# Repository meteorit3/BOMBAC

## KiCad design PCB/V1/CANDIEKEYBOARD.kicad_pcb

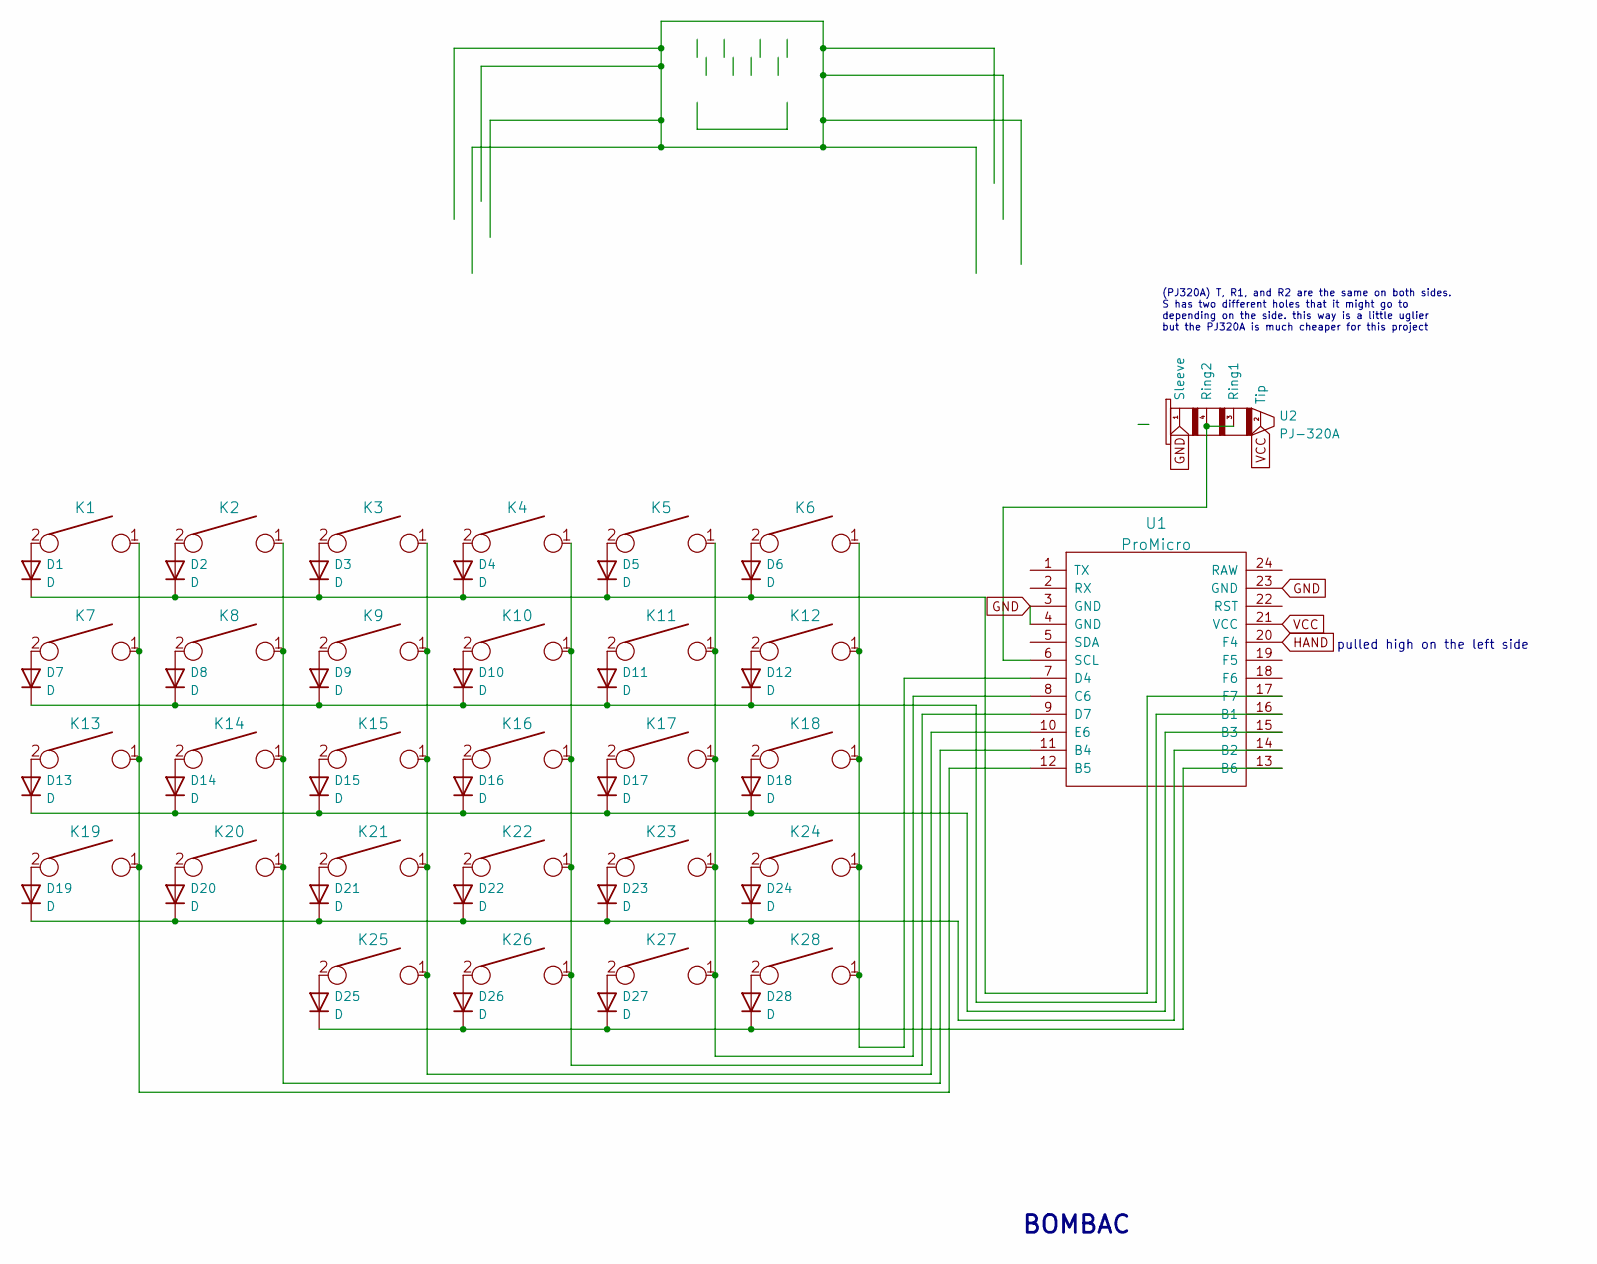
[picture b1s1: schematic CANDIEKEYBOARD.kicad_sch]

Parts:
D1, D2, D3, D4, D5, D6, D7, D8, D9, D10, D11, D12, D13, D14, D15, D16, D17, D18, D19, D20, D21, D22, D23, D24, D25, D26, D27, D28: D; D_DO-35_SOD27_P7.62mm_Horizontal
K1, K2, K3, K4, K5, K6, K7, K8, K9, K10, K11, K12, K13, K14, K15, K16, K17, K18, K19, K20, K21, K22, K23, K24, K25, K26: KEYSW; Mx_Alps_100_Symmetrical
K27: KEYSW; Mx_Alps_200_Symmetrical
K28: KEYSW; Mx_Alps_150_Symmetrical
U1: ProMicro; ProMicro-NoSilk
U2: PJ-320A; PJ-320A_S

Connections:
GND: U1.3 (GND), U1.4 (GND), U1.23 (GND), U2.1 (Sleeve)
HAND: U1.20 (F4)
unnamed: D1.1 (K), D2.1 (K), D3.1 (K), D4.1 (K), D5.1 (K), D6.1 (K), U1.17 (F7)
unnamed: D1.2 (A), K1.2
unnamed: D2.2 (A), K2.2
unnamed: D3.2 (A), K3.2
unnamed: D4.2 (A), K4.2
unnamed: D5.2 (A), K5.2
unnamed: D6.2 (A), K6.2
unnamed: D7.2 (A), K7.2
unnamed: D8.2 (A), K8.2
unnamed: D9.2 (A), K9.2
unnamed: D7.1 (K), D8.1 (K), D9.1 (K), D10.1 (K), D11.1 (K), D12.1 (K), U1.16 (B1)
unnamed: D10.2 (A), K10.2
unnamed: D11.2 (A), K11.2
unnamed: D12.2 (A), K12.2
unnamed: D13.1 (K), D14.1 (K), D15.1 (K), D16.1 (K), D17.1 (K), D18.1 (K), U1.15 (B3)
unnamed: D13.2 (A), K13.2
unnamed: D14.2 (A), K14.2
unnamed: D15.2 (A), K15.2
unnamed: D16.2 (A), K16.2
unnamed: D17.2 (A), K17.2
unnamed: D18.2 (A), K18.2
unnamed: D19.2 (A), K19.2
unnamed: D20.2 (A), K20.2
unnamed: D21.2 (A), K21.2
unnamed: D22.2 (A), K22.2
unnamed: D23.2 (A), K23.2
unnamed: D24.2 (A), K24.2
unnamed: D25.2 (A), K25.2
unnamed: D26.2 (A), K26.2
unnamed: D27.2 (A), K27.2
unnamed: D28.2 (A), K28.2
unnamed: K1.1, K7.1, K13.1, K19.1, U1.12 (B5)
unnamed: K4.1, K10.1, K16.1, K22.1, K26.1, U1.9 (D7)
unnamed: K5.1, K11.1, K17.1, K23.1, K27.1, U1.8 (C6)
unnamed: K6.1, K12.1, K18.1, K24.1, K28.1, U1.7 (D4)
unnamed: K2.1, K8.1, K14.1, K20.1, U1.11 (B4)
unnamed: K3.1, K9.1, K15.1, K21.1, K25.1, U1.10 (E6)
unnamed: U1.6 (SCL), U2.3 (Ring1), U2.4 (Ring2)
unnamed: D25.1 (K), D26.1 (K), D27.1 (K), D28.1 (K), U1.13 (B6)
unnamed: D19.1 (K), D20.1 (K), D21.1 (K), D22.1 (K), D23.1 (K), D24.1 (K), U1.14 (B2)
VCC: U1.21 (VCC), U2.2 (Tip)

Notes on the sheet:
pulled high on the left side
(PJ320A) T, R1, and R2 are the same on both sides. S has two different holes that it might go to depending on the side. this way is a little uglier but the PJ320A is much cheaper for this project
BOMBAC

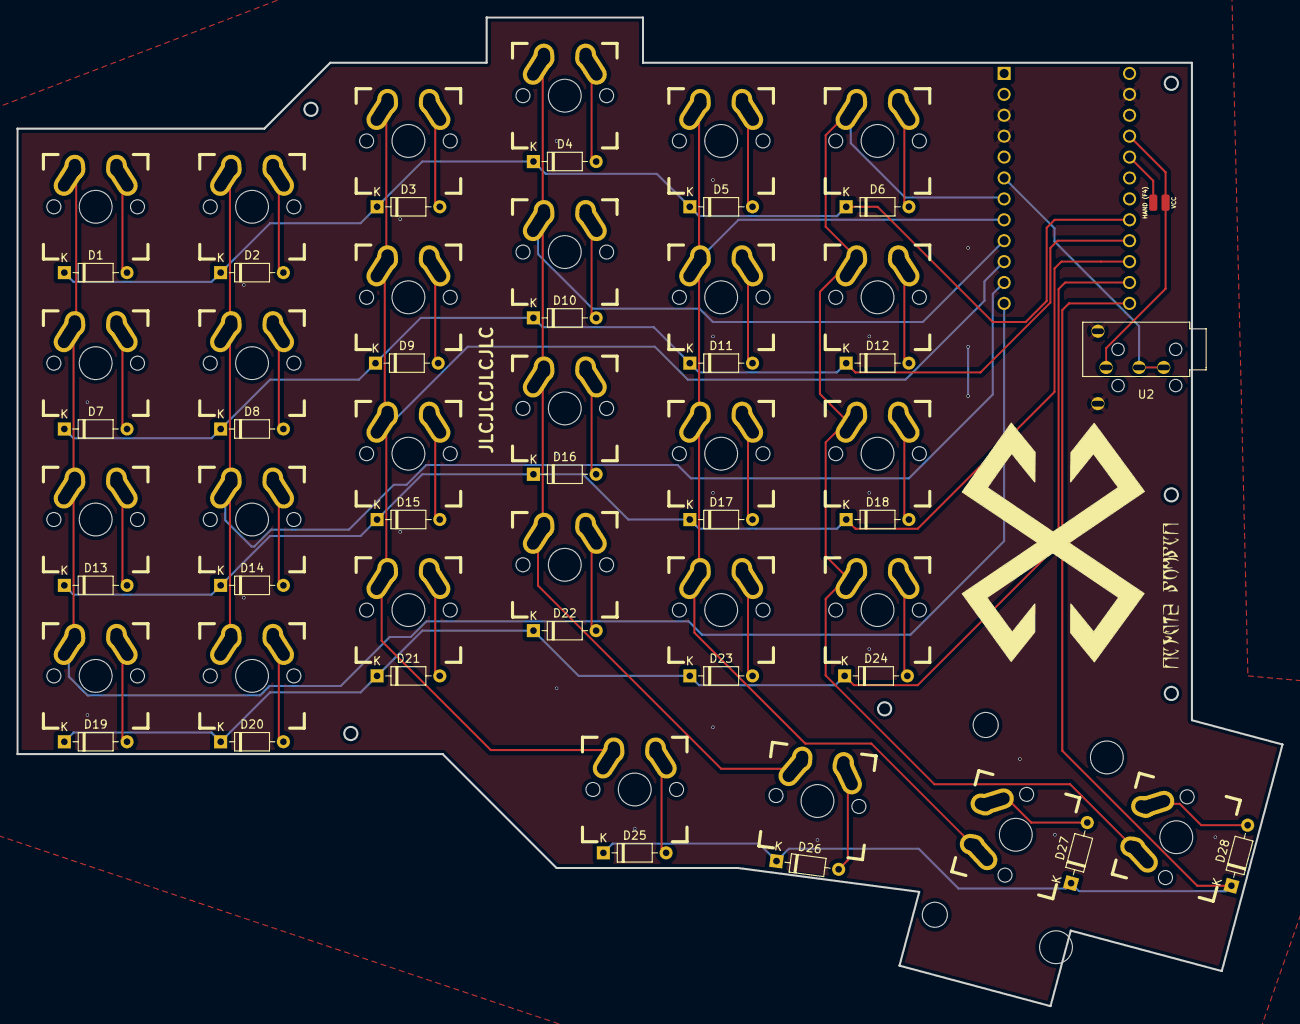
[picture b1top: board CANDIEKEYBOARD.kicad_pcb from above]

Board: 2 copper layers, 153.7 x 120.1 mm, 58 parts (0 on the bottom side), 42 nets.

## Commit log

2022-04-18 deleted extra files and made a new folder for v1 to live in
2022-04-20 A FOLDER FOR CANDIES CODE TO GO IN
2022-04-20 V1 firmware
2022-04-20 REMOVED EMPTY FOLDER
2022-04-20 gaming
